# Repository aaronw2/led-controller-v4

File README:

ESP32-Wrover I/Os

IO0:  (/program), /INT
IO1:  SDA, J107 pin 5
IO2:  SCL, J107 pin 4
IO3:  Fan PWM
IO4:  3.3V I/O J108 pin 8
IO5:  3.3V I/O J108 pin 7
IO6:  5V I/O J108 pin 6
IO7:  5V I/O J108 pin 5
IO8:  I2S1 BCLK (stereo speaker J304)
IO9:  Micro SD D1
IO10: Micro SD D0
IO11: Micro SD CLK
IO12: Micro SD CMD
IO13: Micro SD D3
IO14: Micro SD D2
IO15: 5v I/O J108 pin 4
IO16: 5v I/O J108 pin 3
IO17: I2S1 WSEL (stereo speaker J304)
IO18: I2S1 DOUT (stereo speaker J304)
IO19: USB D-
IO20: USB D+
IO21: Status LED, LED output to J103 pin 2
IO38: /INT2
IO39: M_BOOT_LOAD, BNO085 motion sensor
IO40: AMP power
IO41: /INT3
IO42: BNO085 reset
IO45: I2S0 BCLK (Microphone)
IO46: 12V power supply enable high
IO47: I2S0 WSEL (Microphone)
IO48: I2S0 DIN (Microphone)
RXD0: Serial port RX (can be GPIO)
TXD0: Serial port TX (can be GPIO)
EN: /RESET

Bootstrap:

Boot mode:  IO0  IO46
SPI Boot    1    X
Download    0    0

VDD SPI voltage:
IO45: 0 = 3.3V, 1 = 1.8V

JTAG:
IO3:  0 = JTAG pins, 1 = USB Serial/JTAG

Reset:
The reset signal is driven by the reset button, Q101 via the serial
port RTS/DTR signals, and from the power good output of the 3.3V power supply.
The reset signal drives the reset inputs of the BNO085 motion controller,
the PCA9575 GPIO expander, and the ESP32 S3.  Note that IO2 can also reset
the BNO085 to support loading the bootloader from the ESP32.

Power:
All power is supplied at 5V from either J105, micro USB J104, or USB J102.
J105 is the preferred power source.  5V is converted to 3.3V by the
MPM3810GQB-33 module which provides up to 1.2A.  The power good signal from
this module drives the reset signal so the chip will not be brought out of
reset until after the 3.3V has stabilized.  The 12V supply can provide up to
1A and by default is disabled until IO46 is pulled high.  IO46 is low by
default since it is used for bootstrapping.  This is separate from the fan
PWM which is cointrolled by IO3.

While the board has been configured to handle at least 2A of power at 5V,
this board is not designed to provide power to a significant number of LEDs
or devices.  It is expected that they will have their own power supply with
a common ground.

Fans:
This board provides two outputs for fans.  The first, J201, provides 12V
without PWM support whenever IO46 is pulled high.  Connector J401 provides
both 5V and 12V and both supplies are modulated or controlled by GPIO IO3
which must be pulled high.  IO3 controls both 5V and 12V simultaneously.
The fan outputs have diodes to protect against any back EMF.  The 12V comes
from the same supply and is limited to 1 amp, however it is best to not test
this. The PWM output is driven by IO3. Smoothing capacitors are also in place.

I2C:
The I2C bus uses 2.2K pull-up resistors instead of the more traditional 4.7
or 10K.  This is due to the fact that the i2c bus can be exported off of the
board and having stronger pull-ups should provide better signal integrity.
There are three interrupt lines that are supported.  Internally, i2c is
used by the GPIO expander, the motion sensor, and the I2S stereo audio
amplifier.

I2C is configured such that it can be accessed by the RTC controller, however,
not all of the interrupt inputs are available.

5V signalling:
Six GPIOs pass through open-collector level shifters with pull-up resistors.
These may be used to drive NeoPixels or other 5V devices and are
bi-directional.  All 5V I/Os also have a 33 ohm resistor in series to help
reduce reflections.

Status LED:
A WS2812 compatible status LED is present and is driven by IO21.  The output
of this LED may be used to drive additional LEDs and is connected to J103.

USB:
The USB is connected to the ESP32 controller after passing through a protection
and USB termination chip U101. USB can be used for JTAG and serial output.

Buttons:
Reset - Pulls the reset signal low
Prog - Pulls IO0 low to boot into programming mode.  Since IO0 is also the
INT signal it can be used to generate an interrupt at runtime.  Note that
INT is shared with the I2C GPIO expander.

I2C GPIO Expander:
A SX1509B provides 12 additional GPIO pins which may be configured for input
or output.  They can also be configured to generate an interrupt on the INT
signal (IO0).  The GPIO expander chip is also connected to the reset signal.
This particular GPIO expander has numerous features which may be of use.
It has support for driving LEDs and providing PWM and blink support.  Some
GPIO pins can also "breathe" where they will fade in and out.  Both logrithmic
and linear modes are supported.  It can also function as a keyboard scanner.
Each pin can be input or output, or open drain.  Pull-up and pull-down resistors
can also be configured.
Drive strength and slew rate can also be configured.
Interrupts can be generated on either the rising, falling, or both edges.

Motion Controller/Accelerometer:
A BNO085 9-axis accelerometer/gyroscope/compass/temperature sensor chip is
provided for tracking motion.  This chip performs all the necessary
calculations and offloads them from the ESP32.  It is connected via I2C and
INT2.  The boot loader pin is also connected to a GPIO pin.

Temperature/Pressure/Humidity:
A BME280 temperature, pressure, and humidity sensor is connected to the
secondary I2C bus of the BNO085.  The BNO085 will periodically poll this
and can use this to assist in detecting altitude.

I2C Addresses:
SX1509B: 0x3E
BNO085 motion sensor: 0x29
SSM2518CPZ: 0x36

ESP32 GPIO pins by function:

I2C:
SCL: IO2
SDA: IO1
INT: IO0
INT2: IO38
INT3: IO42

Microphone:
The microphone is wired for the left channel.
I2S0_BCLK: IO45
I2S0_WSEL: IO47
I2S0_DIN:  IO48

Amplifier:
The stereo provides stereo output into 4 ohm speakers.
Power: IO1
I2S1_BCLK: IO8
I2S1_WSEL: IO17
I2S1_DOUT: IO18
I2C address: 0x36

Status LED:
IO21

MicroSD:
CLK: IO11
CMD: IO12
D0:  IO10
D1:  IO9
D2:  IO14
D3:  IO13

12V Enable:
EN: IO46

Fan PWM:
PWM: IO3

Motion Sensor:
M_BOOT_LOAD: IO39
Interrupt: INT2
Reset: Reset and IO2
I2C: 0x29

GPIO Expander:
Interrupt: INT
I2C: 0x3E

3V I/O Pins:
IO4
IO5

5V digital I/O Pins:
IO6
IO7
IO15
IO16

Program: IO0, /INT

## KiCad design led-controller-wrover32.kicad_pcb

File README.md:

ESP32-Wrover I/Os

IO0: (/program), /INT
IO2: 5V enable J107 pin 1
IO3: Fan PWM
IO4: 5V I/O J108 pin 8
IO5: 5V I/O J108 pin 7
IO6: 5V output J108 pin 6
IO7: 5V output J108 pin 5
IO8: I2S1 BCLK (stereo speaker J304)
IO9: Micro SD D1
IO10: Micro SD D0
IO11: Micro SD CLK
IO12: Micro SD CMD
IO13: Micro SD D3
IO14: Micro SD D2
IO15: 5v output J108 pin 4
IO16: 5v output J108 pin 3
IO17: I2S1 WSEL (stereo speaker J304)
IO18: I2S1 DOUT (stereo speaker J304)
IO19: USB D-
IO20: USB D+
IO21: Status LED, LED output to J103 pin 2
IO38: /INT2
IO39: M_BOOT_LOAD, BNO085 motion sensor
IO40: I2C SDA, J107 pin 5
IO41: I2C SCL, J107 pin 4
IO42: /INT3, J107 pin 3
IO45: I2S0 BCLK (Microphone)
IO46: 12V power supply enable high
IO47: I2S0 WSEL (Microphone)
IO48: I2S0 DIN (Microphone)
RXD0: Serial port RX
TXD0: Serial port TX
EN: /RESET

Bootstrap:

Boot mode:  IO0  IO46
SPI Boot    1    X
Download    0    0

VDD SPI voltage:
IO45: 0 = 3.3V, 1 = 1.8V

JTAG:
IO3:  0 = JTAG pins, 1 = USB Serial/JTAG

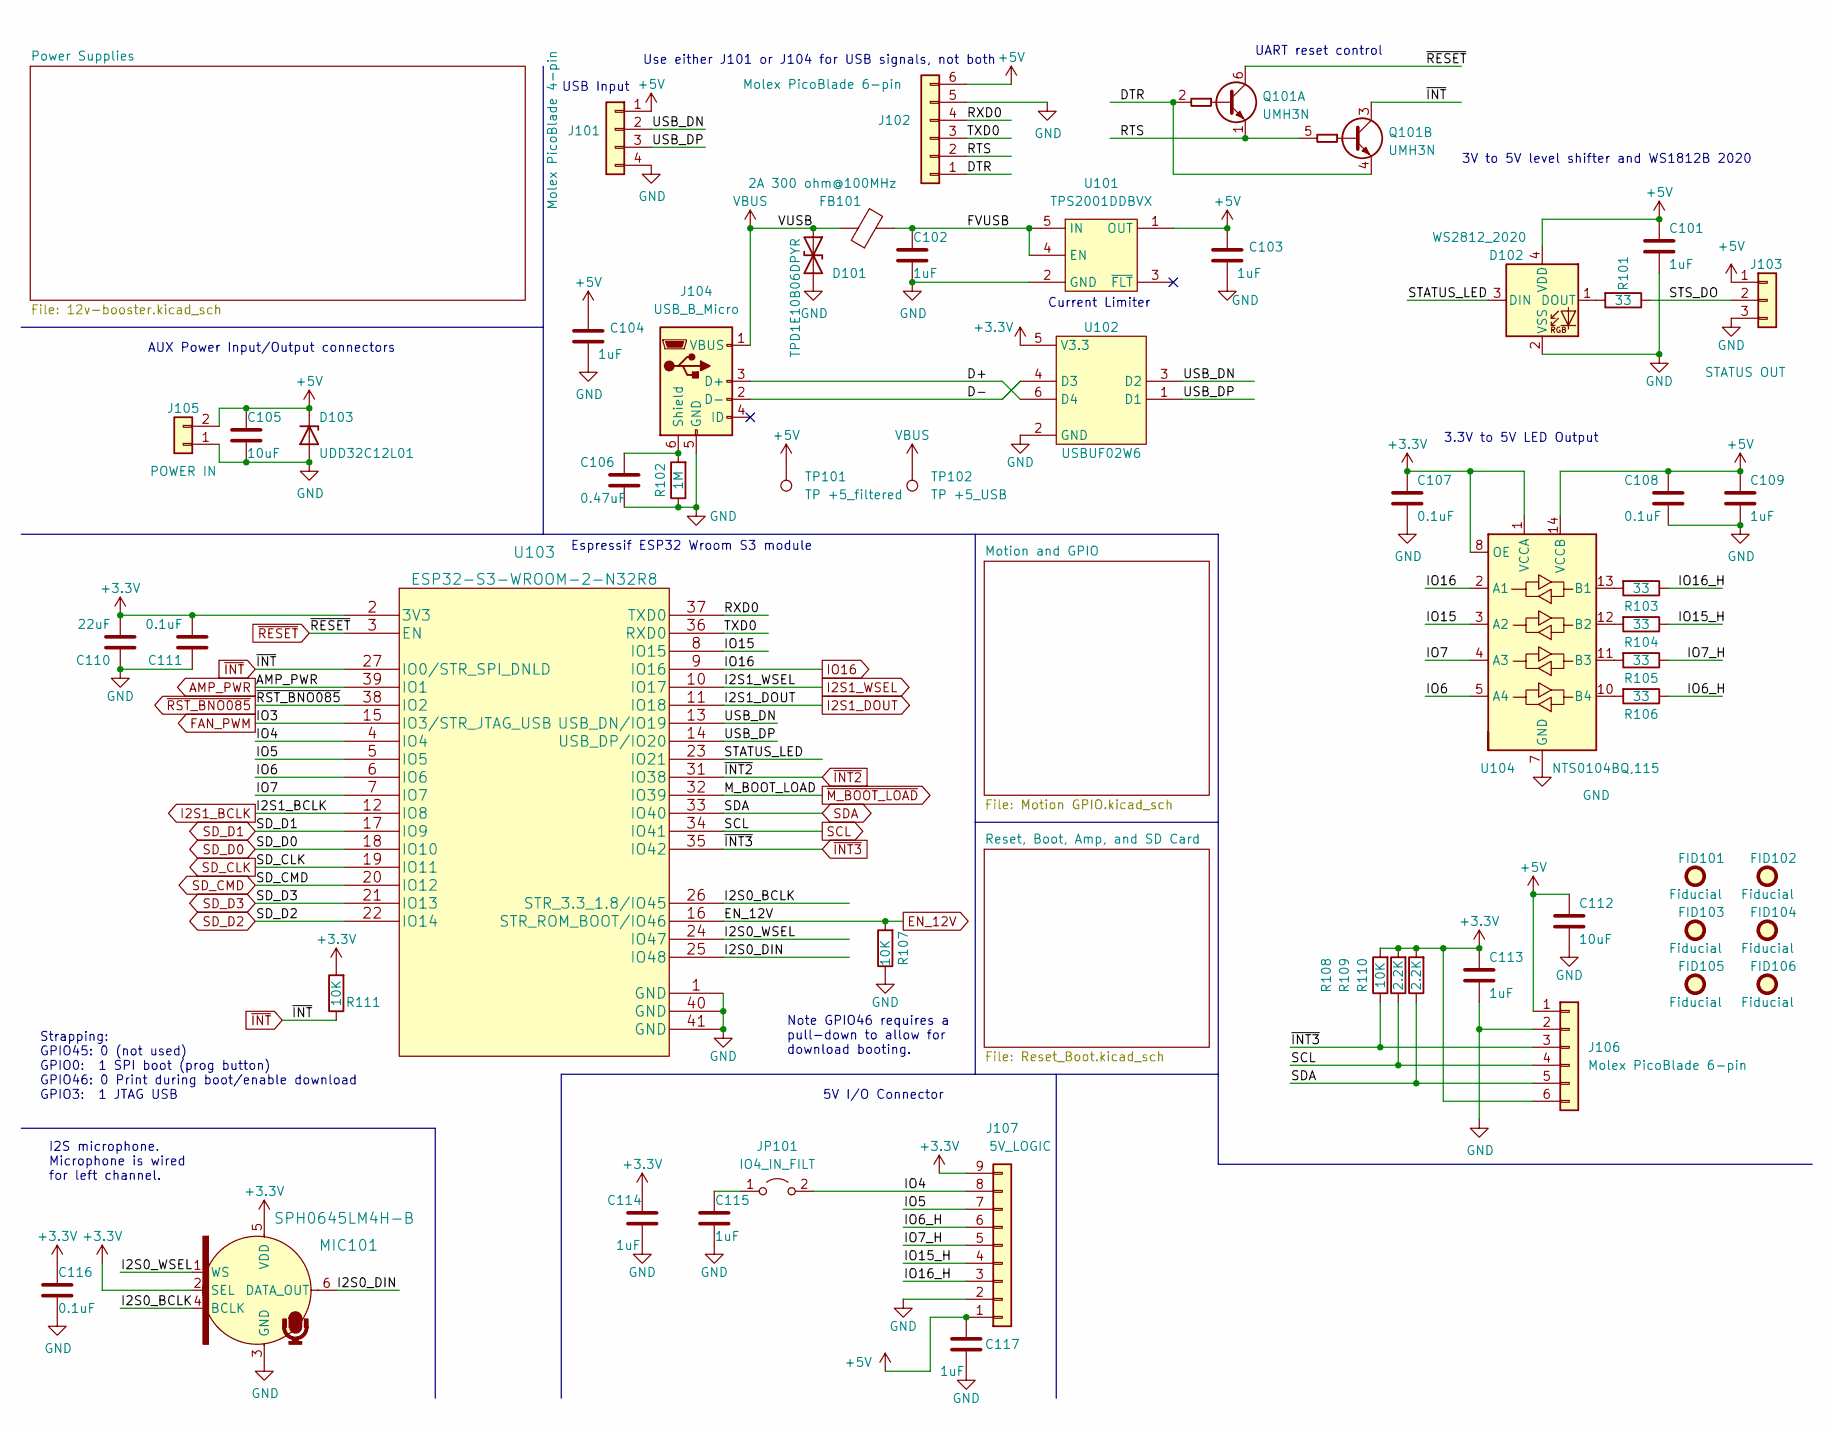
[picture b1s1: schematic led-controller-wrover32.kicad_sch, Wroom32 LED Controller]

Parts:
C101, C102, C103, C104, C109, C113, C114, C115, C117: 1uF; C_0402_1005Metric; MPN GRM155R61E105MA12J; Digi-Key_PN 490-GRM155R61E105MA12JCT-ND
C105, C112: 10uF; C_0402_1005Metric; Digi-Key_PN 1276-1450-1-ND
C106: 0.47uF; C_0402_1005Metric
C107, C108, C111, C116: 0.1uF; C_0402_1005Metric
C110: 22uF; C_0603_1608Metric; MPN CL10A226MO7JZNC; Digi-Key_PN 1276-7076-1-ND
D101: TPD1E10B06DPYR; D_0402_1005Metric; MPN TPD1E10B06DPYR
D102: WS2812_2020; LED_WS2812_2020
D103: UDD32C12L01; D_SOD-323
FB101: 2A 300 ohm@100MHz; L_0603_1608Metric; MPN MI0603L301R-10
FID101, FID102, FID103, FID104, FID105, FID106: Fiducial; Fiducial_0.5mm_Mask1mm
J101: Molex PicoBlade 4-pin; Molex_PicoBlade_53047-0410_1x04_P1.25mm_Vertical; MPN 0530470460
J102, J106: Molex PicoBlade 6-pin; Molex_PicoBlade_53047-0610_1x06_P1.25mm_Vertical; MPN 0530470660; Digi-Key_PN 900-0530470660-ND
J103: STATUS OUT; JST_SH_BM03B-SRSS-TB_1x03-1MP_P1.00mm_Vertical; MPN BM03B-SRSS-TBT(LF)(SN)
J104: USB_B_Micro; USB_Micro-B_Molex-105017-0001; MPN 1050170001
J105: POWER IN; Molex_PicoBlade_53047-0210_1x02_P1.25mm_Vertical; MPN 0530470210
J107: 5V_LOGIC; JST_SH_BM09B-SRSS-TB_1x09-1MP_P1.00mm_Vertical; MPN BM09B-SRSS-TB(LF)(SN); Digi-Key_PN 455-1795-1-ND
JP101: IO4_IN_FILT; SolderJumper-2_P1.3mm_Open_RoundedPad1.0x1.5mm
MIC101: SPH0645LM4H-B; Knowles_LGA-6_3.5x2.65mm; MPN SPH0645LM4H-B; Digi-Key_PN 423-1405-1-ND
Q101: UMH3N; SOT-363_SC-70-6; MPN UMH3NFHATN
R101, R103, R104, R105, R106: 33; R_0402_1005Metric
R102: 1M; R_0402_1005Metric
R107, R108, R111: 10K; R_0402_1005Metric; MPN RC0402FR-0710KL; Digi-Key_PN 311-10.0KLRCT-ND
R109, R110: 2.2K; R_0402_1005Metric
TP101: TP +5_filtered; TestPoint_Pad_1.0x1.0mm
TP102: TP +5_USB; TestPoint_Pad_1.0x1.0mm
U101: TPS2001DDBVX; SOT-23-5; MPN TPS2001DDBVR
U102: USBUF02W6; SOT-323-6L; MPN USBUF02W6
U103: ESP32-S3-WROOM-2-N32R8; ESP32-S3-WROOM-2; MPN ESP32-S3-WROOM-2-N32R8
U104: NTS0104BQ,115; SOT-762-1; MPN NTS0104BQ,115

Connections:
+3V3: C107.1, C110.1, C111.1, C113.1, C114.1, C116.1, J106.6, J107.9, MIC101.2 (SEL), MIC101.5 (VDD), R108.2, R109.2, R110.2, R111.2, U102.5 (V3.3), U103.2 (3V3), U104.1 (VCCA), U104.8 (OE); also elsewhere on the board
+5V: C101.1, C103.1, C104.1, C105.1, C108.1, C109.1, C112.1, C117.1, D102.4 (VDD), D103.1 (K), J101.1, J102.6, J103.1, J105.2, J106.1, J107.1, TP101.1, U101.1 (OUT), U104.14 (VCCB); also elsewhere on the board
/D+: J104.3 (D+), U102.6 (D4)
/D-: J104.2 (D-), U102.4 (D3)
/DTR: J102.1, Q101.2 (B1), Q101.4 (E2)
/FVUSB: C102.1, FB101.2, U101.4 (EN), U101.5 (IN)
/I2S0_BCLK: MIC101.4 (BCLK), U103.26 (STR_3.3_1.8/IO45)
/I2S0_DIN: MIC101.6 (DATA_OUT), U103.25 (IO48)
/I2S0_WSEL: MIC101.1 (WS), U103.24 (IO47)
/IO4: J107.8, JP101.2 (B), U103.4 (IO4)
/IO5: J107.7, U103.5 (IO5)
/IO6: U103.6 (IO6), U104.5 (A4)
/IO6_H: J107.6, R106.1
/IO7: U103.7 (IO7), U104.4 (A3)
/IO7_H: J107.5, R105.1
/IO15: U103.8 (IO15), U104.3 (A2)
/IO15_H: J107.4, R104.1
/IO16_H: J107.3, R103.1
/RTS: J102.2, Q101.1 (E1), Q101.5 (B2)
/RXD0: J102.4, U103.37 (TXD0)
/STATUS_LED: D102.3 (DIN), U103.23 (IO21)
/STS_DO: J103.2, R101.1
/TXD0: J102.3, U103.36 (RXD0)
/USB_DN: J101.2, U102.3 (D2), U103.13 (USB_DN/IO19)
/USB_DP: J101.3, U102.1 (D1), U103.14 (USB_DP/IO20)
AMP_PWR: U103.39 (IO1); also elsewhere on the board
EN_12V: R107.2, U103.16 (STR_ROM_BOOT/IO46); also elsewhere on the board
FAN_PWM: U103.15 (IO3/STR_JTAG_USB); also elsewhere on the board
GND: C101.2, C102.2, C103.2, C104.2, C105.2, C106.2, C107.2, C108.2, C109.2, C110.2, C111.2, C112.2, C113.2, C114.2, C115.2, C116.2, C117.2, D101.2 (A2), D102.2 (VSS), D103.2 (A), J101.4, J102.5, J103.3, J104.5 (GND), J105.1, J106.2, J107.2, MIC101.3 (GND), R102.1, R107.1, U101.2 (GND), U102.2 (GND), U103.1 (GND), U103.40 (GND), U103.41 (GND), U104.7 (GND), U104.15 (GND); also elsewhere on the board
I2S1_BCLK: U103.12 (IO8); also elsewhere on the board
I2S1_DOUT: U103.11 (IO18); also elsewhere on the board
I2S1_WSEL: U103.10 (IO17); also elsewhere on the board
IO16: U103.9 (IO16), U104.2 (A1)
unnamed: C106.1, J104.6 (Shield), R102.2
unnamed: C115.1, JP101.1 (A)
unnamed: D102.1 (DOUT), R101.2
unnamed: R103.2, U104.13 (B1)
unnamed: R104.2, U104.12 (B2)
unnamed: R105.2, U104.11 (B3)
unnamed: R106.2, U104.10 (B4)
SCL: J106.4, R109.1, U103.34 (IO41); also elsewhere on the board
SDA: J106.5, R110.1, U103.33 (IO40); also elsewhere on the board
SD_CLK: U103.19 (IO11); also elsewhere on the board
SD_CMD: U103.20 (IO12); also elsewhere on the board
SD_D0: U103.18 (IO10); also elsewhere on the board
SD_D1: U103.17 (IO9); also elsewhere on the board
SD_D2: U103.22 (IO14); also elsewhere on the board
SD_D3: U103.21 (IO13); also elsewhere on the board
VBUS: D101.1 (A1), FB101.1, J104.1 (VBUS), TP102.1
~INT2: U103.31 (IO38); also elsewhere on the board
~INT3: J106.3, R108.1, U103.35 (IO42)
~INT: Q101.3 (C2), R111.1, U103.27 (IO0/STR_SPI_DNLD); also elsewhere on the board
~M_BOOT_LOAD: U103.32 (IO39); also elsewhere on the board
~RESET: Q101.6 (C1), U103.3 (EN); also elsewhere on the board
~RST_BNO085: U103.38 (IO2); also elsewhere on the board

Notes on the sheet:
Espressif ESP32 Wroom S3 module
3V to 5V level shifter and WS1812B 2020
I2S microphone. Microphone is wired for left channel.
Strapping: GPIO45: 0 (not used) GPIO0: 1 SPI boot (prog button) GPIO46: 0 Print during boot/enable download GPIO3: 1 JTAG USB
Current Limiter
3.3V to 5V LED Output
Use either J101 or J104 for USB signals, not both
5V I/O Connector
AUX Power Input/Output connectors
UART reset control
Note GPIO46 requires a pull-down to allow for download booting.
USB Input

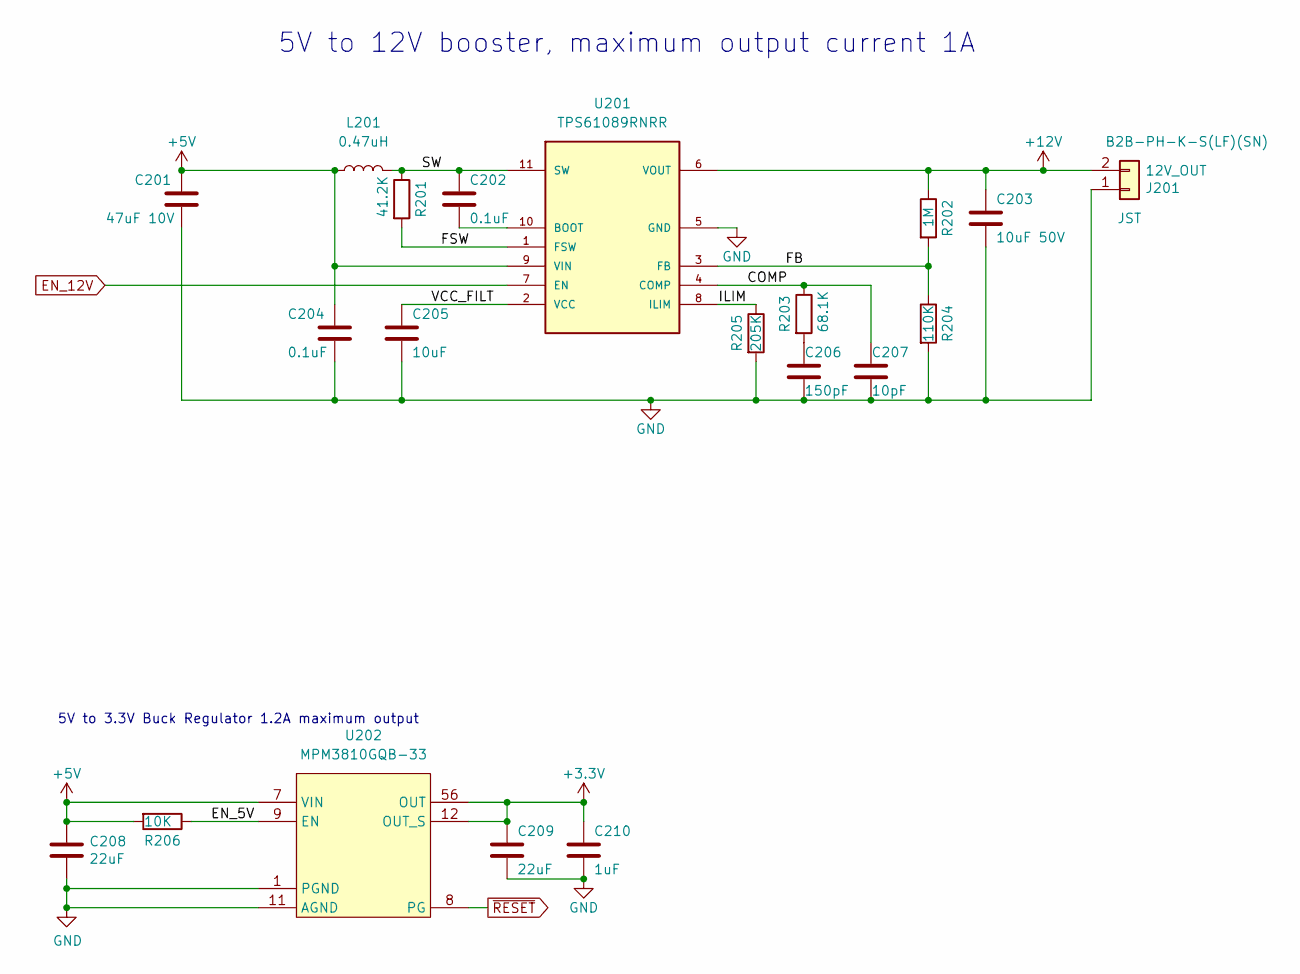
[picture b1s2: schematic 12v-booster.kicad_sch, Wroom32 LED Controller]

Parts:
C201: 47uF 10V; C_0805_2012Metric; MPN GRM21BR61A476ME15L
C202, C204: 0.1uF; C_0402_1005Metric
C203: 10uF 50V; C_0805_2012Metric; MPN GRM21BR61H106KE43L
C205: 10uF; C_0402_1005Metric; Digi-Key_PN 1276-1450-1-ND
C206: 150pF; C_0402_1005Metric
C207: 10pF; C_0402_1005Metric
C208, C209: 22uF; C_0603_1608Metric; MPN CL10A226MO7JZNC; Digi-Key_PN 1276-7076-1-ND
C210: 1uF; C_0402_1005Metric; MPN GRM155R61E105MA12J; Digi-Key_PN 490-GRM155R61E105MA12JCT-ND
J201: 12V_OUT; JST_PH_B2B-PH-K_1x02_P2.00mm_Vertical; MPN B2B-PH-K-S(LF)(SN)
L201: 0.47uH; L_Bourns_SRP3212; MPN SRP3212-R47M; Digi-Key_PN 118-SRP3212-R47MCT-ND
R201: 41.2K; R_0402_1005Metric
R202: 1M; R_0402_1005Metric
R203: 68.1K; R_0402_1005Metric
R204: 110K; R_0402_1005Metric
R205: 205K; R_0402_1005Metric
R206: 10K; R_0402_1005Metric; MPN RC0402FR-0710KL; Digi-Key_PN 311-10.0KLRCT-ND
U201: TPS61089RNRR; Texas_S_VQFN-11_2.0x2.5mm_P0.5mm_Thermal; PARTREV B
U202: MPM3810GQB-33; Monolithic_QFN-12-2.5x3.0mm_P0.4mm; MPN MPM3810GQB-33-Z

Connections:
+3V3: C209.1, C210.1, U202.12 (OUT_S), U202.56 (OUT); also elsewhere on the board
+5V: C201.1, C204.1, C208.1, L201.1, R206.2, U201.9 (VIN), U202.7 (VIN); also elsewhere on the board
+12V: C203.1, J201.2, R202.1, U201.6 (VOUT); also elsewhere on the board
/Power Supplies/COMP: C207.1, R203.1, U201.4 (COMP)
/Power Supplies/EN_5V: R206.1, U202.9 (EN)
/Power Supplies/FB: R202.2, R204.1, U201.3 (FB)
/Power Supplies/FSW: R201.2, U201.1 (FSW)
/Power Supplies/ILIM: R205.1, U201.8 (ILIM)
/Power Supplies/SW: C202.1, L201.2, R201.1, U201.11 (SW)
/Power Supplies/VCC_FILT: C205.1, U201.2 (VCC)
EN_12V: U201.7 (EN); also elsewhere on the board
GND: C201.2, C203.2, C204.2, C205.2, C206.2, C207.2, C208.2, C209.2, C210.2, J201.1, R204.2, R205.2, U201.5 (GND), U202.1 (PGND), U202.2 (PGND), U202.11 (AGND); also elsewhere on the board
unnamed: C202.2, U201.10 (BOOT)
unnamed: C206.1, R203.2
~RESET: U202.8 (PG); also elsewhere on the board

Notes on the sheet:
5V to 3.3V Buck Regulator 1.2A maximum output
5V to 12V booster, maximum output current 1A

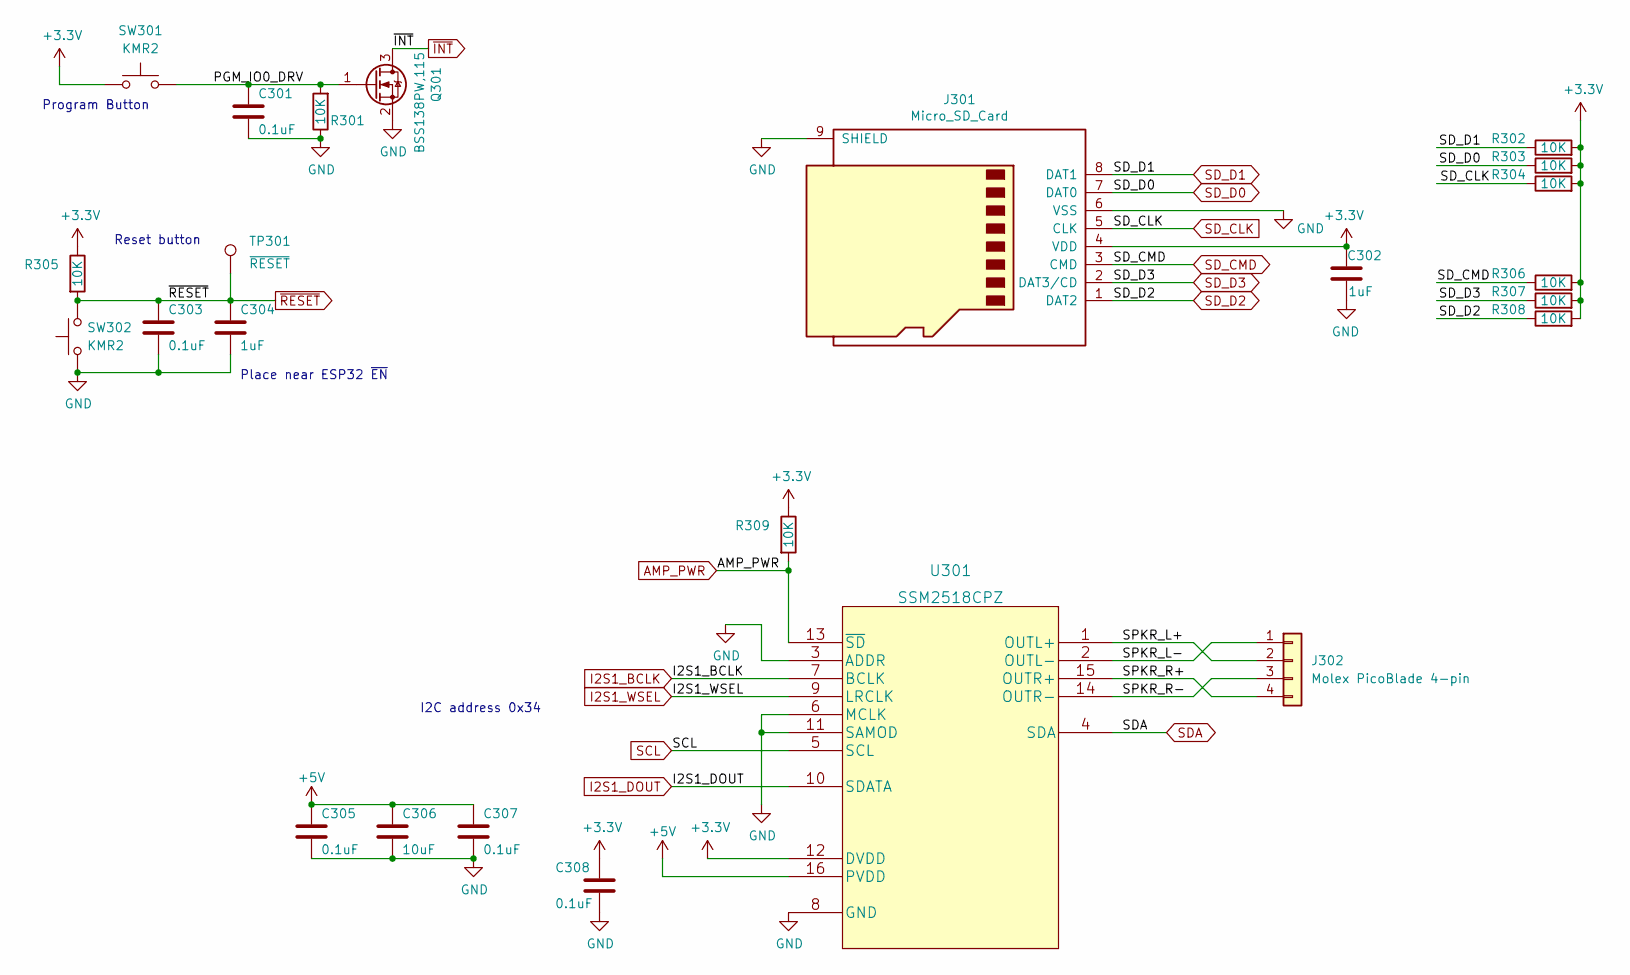
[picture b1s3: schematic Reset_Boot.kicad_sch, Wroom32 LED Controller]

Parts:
C301, C303, C305, C307, C308: 0.1uF; C_0402_1005Metric
C302, C304: 1uF; C_0402_1005Metric; MPN GRM155R61E105MA12J; Digi-Key_PN 490-GRM155R61E105MA12JCT-ND
C306: 10uF; C_0402_1005Metric; Digi-Key_PN 1276-1450-1-ND
J301: Micro_SD_Card; microSD_HC_Molex_047571-0001; MPN 0475710001
J302: Molex PicoBlade 4-pin; Molex_PicoBlade_53047-0410_1x04_P1.25mm_Vertical; MPN 0530470460
Q301: BSS138PW,115; SOT-323_SC-70; MPN BSS138PW,115; Digi-Key_PN 1727-1143-1-ND
R301, R302, R303, R304, R305, R306, R307, R308, R309: 10K; R_0402_1005Metric; MPN RC0402FR-0710KL; Digi-Key_PN 311-10.0KLRCT-ND
SW301, SW302: KMR2; SW_Push_1P1T_NO_CK_KMR2
TP301: ~{RESET}; TestPoint_Pad_1.0x1.0mm
U301: SSM2518CPZ; LFCSP-20-1EP_4x4mm_P0.5mm_EP2.6x2.6mm; MPN SSM2518CPZ

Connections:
+3V3: C302.1, C308.1, J301.4 (VDD), R302.2, R303.2, R304.2, R305.1, R306.2, R307.2, R308.2, R309.1, SW301.1, U301.12 (DVDD); also elsewhere on the board
+5V: C305.1, C306.1, C307.1, U301.16 (PVDD), U301.20 (PVDD); also elsewhere on the board
/Reset, Boot, Amp, and SD Card/PGM_IO0_DRV: C301.1, Q301.1 (G), R301.2, SW301.2
/Reset, Boot, Amp, and SD Card/SPKR_L+: J302.2, U301.1 (OUTL+)
/Reset, Boot, Amp, and SD Card/SPKR_L-: J302.1, U301.2 (OUTL-)
/Reset, Boot, Amp, and SD Card/SPKR_R+: J302.4, U301.15 (OUTR+)
/Reset, Boot, Amp, and SD Card/SPKR_R-: J302.3, U301.14 (OUTR-)
AMP_PWR: R309.2, U301.13 (~SD); also elsewhere on the board
GND: C301.2, C302.2, C303.2, C304.2, C305.2, C306.2, C307.2, C308.2, J301.6 (VSS), J301.9 (SHIELD), Q301.2 (S), R301.1, SW302.1, U301.3 (ADDR), U301.6 (MCLK), U301.8 (GND), U301.11 (SAMOD), U301.17 (GND), U301.18 (GND), U301.19 (GND), U301.21 (GND); also elsewhere on the board
I2S1_BCLK: U301.7 (BCLK); also elsewhere on the board
I2S1_DOUT: U301.10 (SDATA); also elsewhere on the board
I2S1_WSEL: U301.9 (LRCLK); also elsewhere on the board
SCL: U301.5 (SCL); also elsewhere on the board
SDA: U301.4 (SDA); also elsewhere on the board
SD_CLK: J301.5 (CLK), R304.1; also elsewhere on the board
SD_CMD: J301.3 (CMD), R306.1; also elsewhere on the board
SD_D0: J301.7 (DAT0), R303.1; also elsewhere on the board
SD_D1: J301.8 (DAT1), R302.1; also elsewhere on the board
SD_D2: J301.1 (DAT2), R308.1; also elsewhere on the board
SD_D3: J301.2 (DAT3/CD), R307.1; also elsewhere on the board
~INT: Q301.3 (D); also elsewhere on the board
~RESET: C303.1, C304.1, R305.2, SW302.2, TP301.1; also elsewhere on the board

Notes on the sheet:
Program Button
Place near ESP32 ~{EN}
Reset button
I2C address 0x34

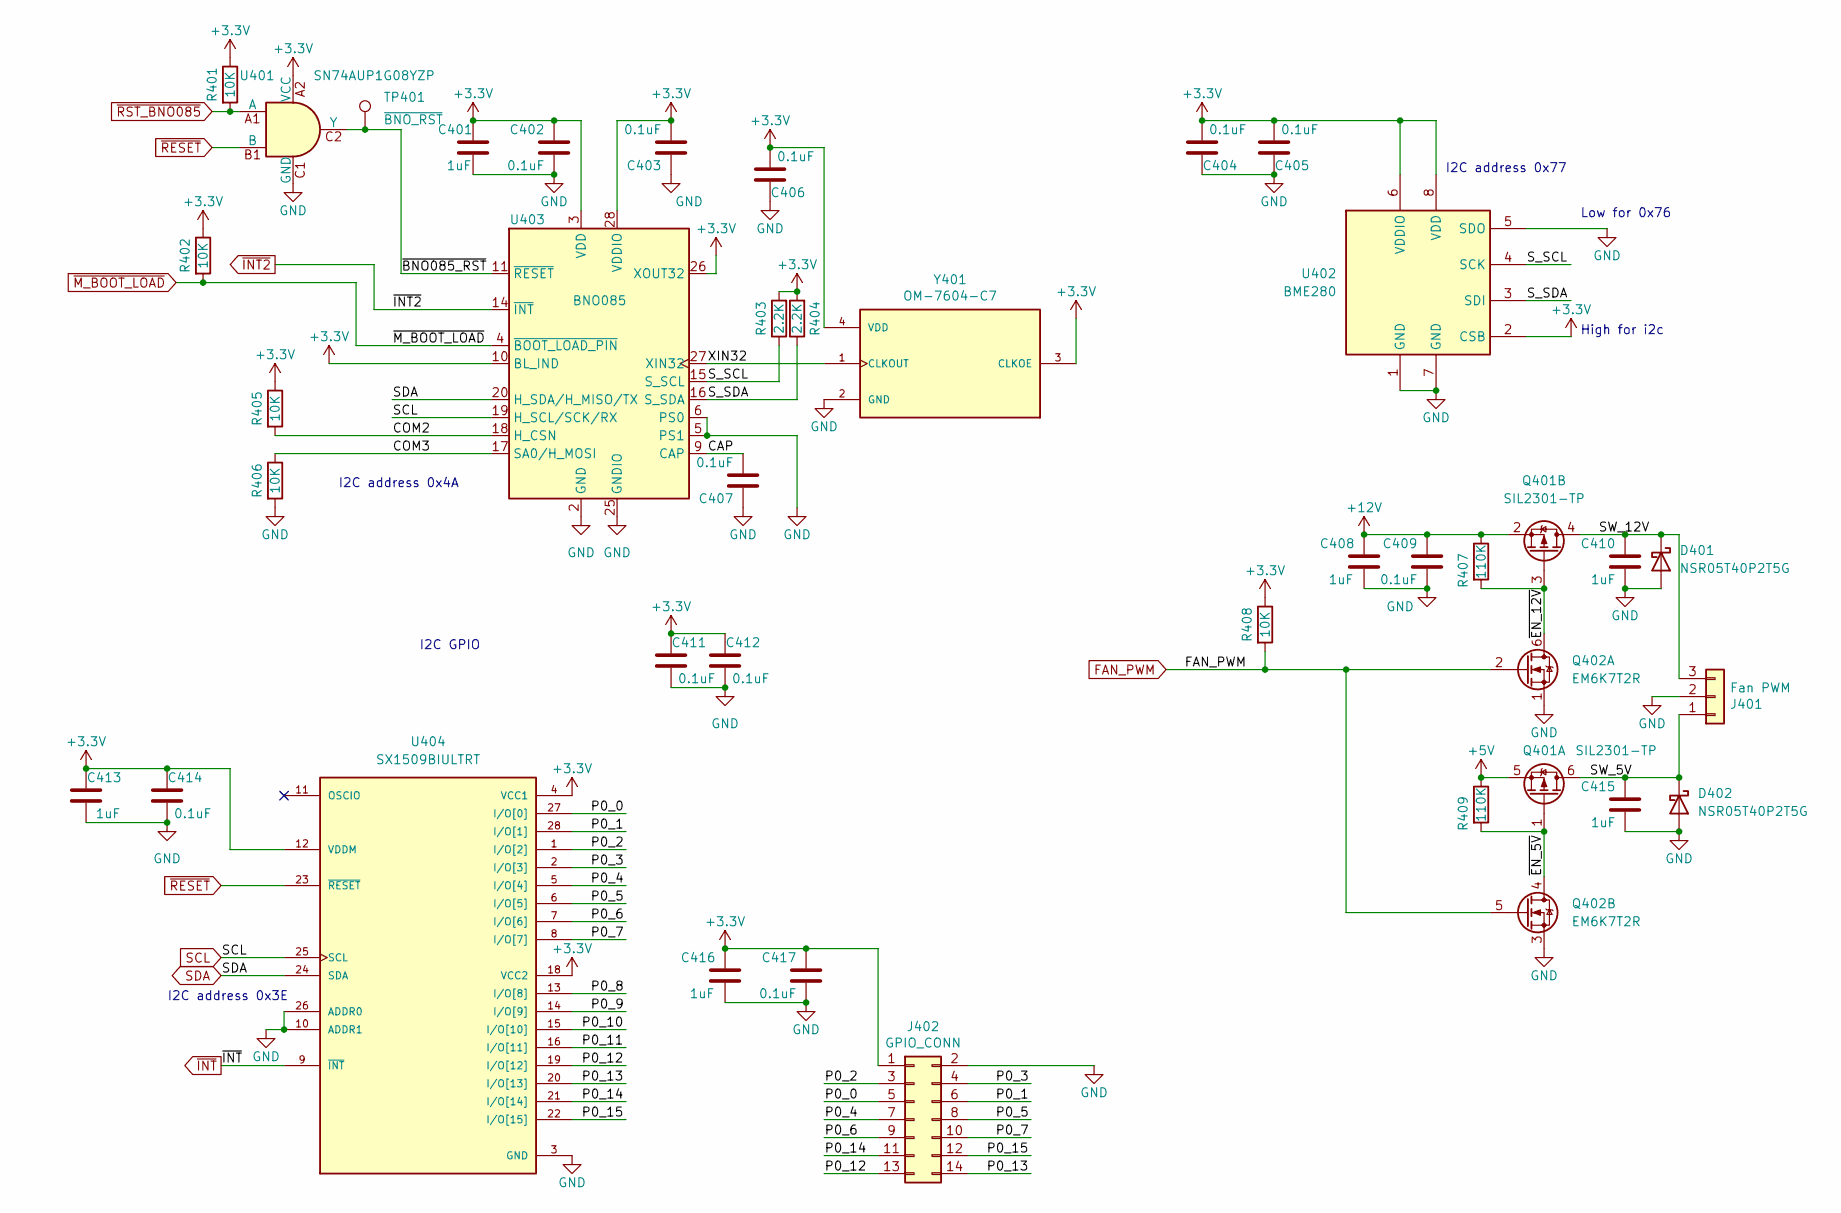
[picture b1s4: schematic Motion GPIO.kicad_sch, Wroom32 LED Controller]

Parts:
C401, C408, C410, C413, C415, C416: 1uF; C_0402_1005Metric; MPN GRM155R61E105MA12J; Digi-Key_PN 490-GRM155R61E105MA12JCT-ND
C402, C403, C404, C405, C406, C407, C409, C411, C412, C414, C417: 0.1uF; C_0402_1005Metric
D401, D402: NSR05T40P2T5G; D_SOD-923; MPN NSR05T40P2T5G
J401: Fan PWM; JST_PH_B3B-PH-K_1x03_P2.00mm_Vertical
J402: GPIO_CONN; PinHeader_2x07_P2.54mm_Vertical; MPN PH2-14-UA
Q401: SIL2301-TP; SOT-23-6; MPN SIL2301-TP
Q402: EM6K7T2R; SOT-563; MPN EM6K7T2R
R401, R402, R405, R406, R408: 10K; R_0402_1005Metric; MPN RC0402FR-0710KL; Digi-Key_PN 311-10.0KLRCT-ND
R403, R404: 2.2K; R_0402_1005Metric
R407, R409: 110K; R_0402_1005Metric
TP401: ~{BNO_RST}; TestPoint_Pad_1.0x1.0mm
U401: SN74AUP1G08YZP; Texas_DSBGA-5_0.9x1.4mm_Layout2x1x2_P0.5mm
U402: BME280; Bosch_LGA-8_2.5x2.5mm_P0.65mm_ClockwisePinNumbering; MPN BME280
U403: BNO085; LGA-28_5.2x3.8mm_P0.5mm; MPN BNO085
U404: SX1509BIULTRT; QFN-28-1EP_4x4mm_P0.4mm_EP2.65x2.65mm; MPN SX1509BIULTRT
Y401: OM-7604-C7; OSC_OM-7604-C7; PARTREV 4.2/06.2019

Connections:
+3V3: C401.1, C402.1, C403.1, C404.1, C405.1, C406.1, C411.1, C412.1, C413.1, C414.1, C416.1, C417.1, J402.1, R401.1, R402.1, R403.2, R404.2, R405.1, R408.1, U401.A2 (VCC), U402.2 (CSB), U402.6 (VDDIO), U402.8 (VDD), U403.3 (VDD), U403.10 (BL_IND), U403.26 (XOUT32), U403.28 (VDDIO), U404.4 (VCC1), U404.12 (VDDM), U404.18 (VCC2), Y401.3 (CLKOE), Y401.4 (VDD); also elsewhere on the board
+5V: Q401.5 (S), R409.1; also elsewhere on the board
+12V: C408.1, C409.1, Q401.2 (S), R407.1; also elsewhere on the board
/Motion and GPIO/CAP: C407.1, U403.9 (CAP)
/Motion and GPIO/COM2: R405.2, U403.18 (H_CSN)
/Motion and GPIO/COM3: R406.1, U403.17 (SA0/H_MOSI)
/Motion and GPIO/P0_0: J402.5, U404.27 (I/O[0])
/Motion and GPIO/P0_1: J402.6, U404.28 (I/O[1])
/Motion and GPIO/P0_2: J402.3, U404.1 (I/O[2])
/Motion and GPIO/P0_3: J402.4, U404.2 (I/O[3])
/Motion and GPIO/P0_4: J402.7, U404.5 (I/O[4])
/Motion and GPIO/P0_5: J402.8, U404.6 (I/O[5])
/Motion and GPIO/P0_6: J402.9, U404.7 (I/O[6])
/Motion and GPIO/P0_7: J402.10, U404.8 (I/O[7])
/Motion and GPIO/P0_8: U404.13 (I/O[8])
/Motion and GPIO/P0_9: U404.14 (I/O[9])
/Motion and GPIO/P0_10: U404.15 (I/O[10])
/Motion and GPIO/P0_11: U404.16 (I/O[11])
/Motion and GPIO/P0_12: J402.13, U404.19 (I/O[12])
/Motion and GPIO/P0_13: J402.14, U404.20 (I/O[13])
/Motion and GPIO/P0_14: J402.11, U404.21 (I/O[14])
/Motion and GPIO/P0_15: J402.12, U404.22 (I/O[15])
/Motion and GPIO/SW_5V: C415.1, D402.1 (K), J401.1, Q401.6 (D)
/Motion and GPIO/SW_12V: C410.1, D401.1 (K), J401.3, Q401.4 (D)
/Motion and GPIO/S_SCL: R403.1, U402.4 (SCK), U403.15 (S_SCL)
/Motion and GPIO/S_SDA: R404.1, U402.3 (SDI), U403.16 (S_SDA)
/Motion and GPIO/XIN32: U403.27 (XIN32), Y401.1 (CLKOUT)
/Motion and GPIO/~BNO085_RST: TP401.1, U401.C2 (Y), U403.11 (~RESET)
/Motion and GPIO/~EN_5V: Q401.1 (G), Q402.4 (D), R409.2
/Motion and GPIO/~EN_12V: Q401.3 (G), Q402.6 (D), R407.2
FAN_PWM: Q402.2 (G), Q402.5 (G), R408.2; also elsewhere on the board
GND: C401.2, C402.2, C403.2, C404.2, C405.2, C406.2, C407.2, C408.2, C409.2, C410.2, C411.2, C412.2, C413.2, C414.2, C415.2, C416.2, C417.2, D401.2 (A), D402.2 (A), J401.2, J402.2, Q402.1 (S), Q402.3 (S), R406.2, U401.C1 (GND), U402.1 (GND), U402.5 (SDO), U402.7 (GND), U403.2 (GND), U403.5 (PS1), U403.6 (PS0), U403.25 (GNDIO), U404.3 (GND), U404.10 (ADDR1), U404.17 (GND), U404.26 (ADDR0), U404.29 (GND), Y401.2 (GND); also elsewhere on the board
SCL: U403.19 (H_SCL/SCK/RX), U404.25 (SCL); also elsewhere on the board
SDA: U403.20 (H_SDA/H_MISO/TX), U404.24 (SDA); also elsewhere on the board
~INT2: U403.14 (~INT); also elsewhere on the board
~INT: U404.9 (~INT); also elsewhere on the board
~M_BOOT_LOAD: R402.2, U403.4 (~BOOT_LOAD_PIN); also elsewhere on the board
~RESET: U401.B1 (B), U404.23 (~RESET); also elsewhere on the board
~RST_BNO085: R401.2, U401.A1 (A); also elsewhere on the board

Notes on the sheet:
Low for 0x76
I2C address 0x4A
I2C GPIO
I2C address 0x3E
High for i2c
I2C address 0x77

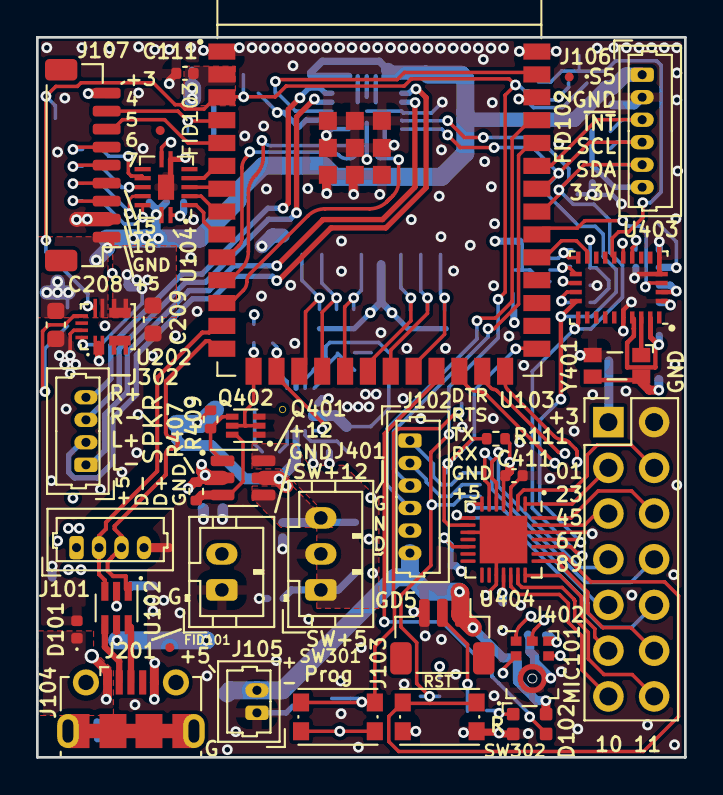
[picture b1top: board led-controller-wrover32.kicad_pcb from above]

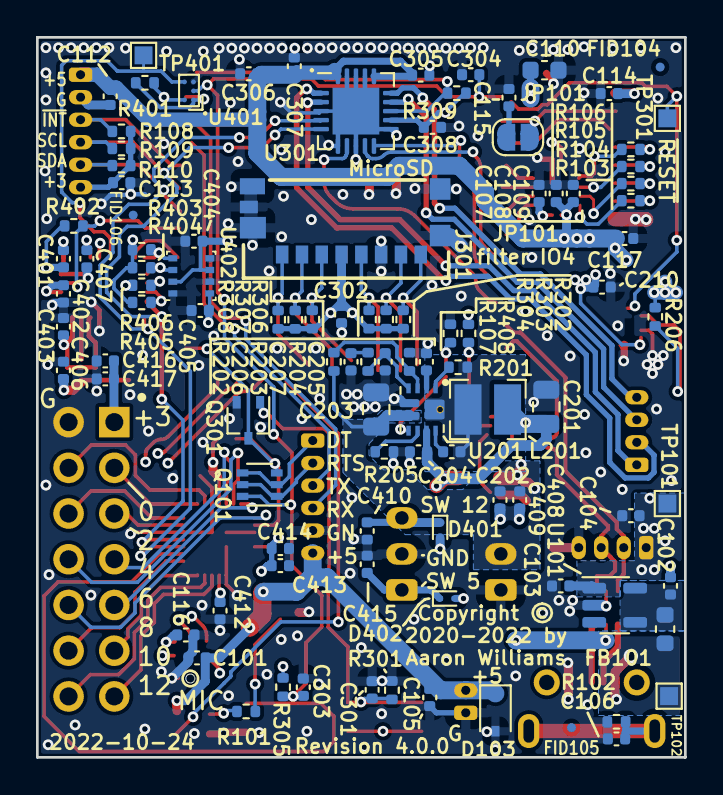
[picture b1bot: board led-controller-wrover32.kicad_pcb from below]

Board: 4 copper layers, 36.0 x 40.0 mm, 136 parts (101 on the bottom side), 93 nets.

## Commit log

2022-05-15 More updates
    - Changed obsolete unidirectional level shifter to open-collector level shifter
    - Replaced BSS138 level shifters with dedicated level shifter
    - Changed all 5V I/O pins to have 33 ohm resistor in series
    - Changed a few capacitors
    - Cleanup tracks, vias, silkscreen, etc.
2022-05-15 Added BOM
2022-05-15 Multiple updates
    - Changed input current limiter to ferrite bead
    - Added pull-up for BNO085 boot mode
    - Minor layout changes
2022-05-16 More updates
    - Removed 5V switch
    - Added manual reset control of BNO085 to support booting remotely
    - More minor cleanups
    - Added jpeg renderings
2022-05-17 Switched to a different 12V booster chip and increased 12V from 500ma to 1A.
    Also:
    - Switched most 10uF capacitors to 0402 footprints.
    - Other cleanup
2022-10-24 Latest 4.0 settings for pcbway
2022-10-25 Minor fixes.
2022-12-03 Moved to ESP32 S3 Wroom 1
    The Wroom 2 requires 1.8V on a couple of GPIOs. Since I don't need 32MB of
    flash the Wroom 1 is used instead. The footprint is slightly different,
    however.
2022-12-06 Changed ESP32 to ESP32-S3-WROOM-1 and other cleanup
2022-12-20 Fixed ESP32 footprint
    Apparently the footprint changed so this reflects the latest update.

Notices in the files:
12v-booster.kicad_sch:
Copyright © 2020-2022 by Aaron Williams
led-controller-wrover32.kicad_pcb:
Copyright ©
